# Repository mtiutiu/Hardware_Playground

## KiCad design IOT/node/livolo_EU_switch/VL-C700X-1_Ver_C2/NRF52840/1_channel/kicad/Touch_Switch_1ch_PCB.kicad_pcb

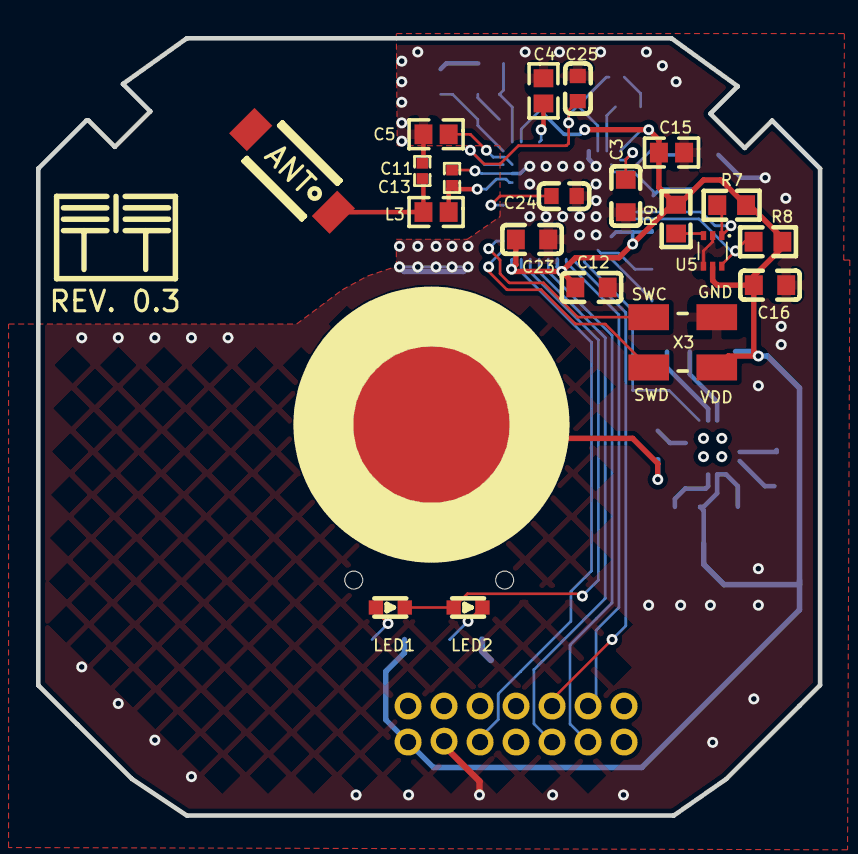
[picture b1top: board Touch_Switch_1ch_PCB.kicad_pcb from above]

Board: 2 copper layers, 43.4 x 43.2 mm, 47 parts (0 on the bottom side), 37 nets.

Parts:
ALG: my_logo; ggeac4e8891367b2b2c
C1, C15, C17: 1uF; 0603
C2, C3, C12, C16, C18, C19, C20, C23: 100nF; C0603
C4: N.C.; 0603
C5: 100pF; 0603
C6: 2.2nF; C0603
C7, C8, C9, C10: 22pF; 0603
C11, C13: 0.5pF; 0402
C14, C21, C22: 4.7uF; 0603
C24: 820pF; C0603
C25: 47nF; C0603
CN1: 2X7P; HDR-TH_14P-P2.00-V-R2-C7-S2.00_A2005HWV-2X7P
H1: PROG; CONNECTER_SMD_1.27_1X4_D180
L2: 10uH; 0603
L3: 3.3nH; 0603
L4: 15nH; 0402
LED1: RED; LED-SMD_0603-T
LED2: BLUE; LED-SMD_0603-T
R5, R6, R7, R8, R9: 4.7K; R0603
R10: 560; R0603
U1: NRF52840-QIAA-R; AQFN-73_L7.0-W7.0-P0.50-BL-EP4.8
U3: Antenna 2.4GHz; AN6520
U5: TMP112; SOT-563_L1.6-W1.2-P0.50-LS1.6-BL
U6: CY8C4014LQI-421T; QFN-16_L3.0-W3.0-P0.50-BL-EP1.7
U7: TS1; LIVOLO_TOUCH_PAD
X1: 32MHz; OSC-SMD_4P-L2.0-W1.6-BL
X2: 32.768KHz; FC-135R_L3.2-W1.5
X3: ICSP; SWD4_5032

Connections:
ANT: C11.1, L3.1, U1.H23
C4_2: C4.2, U1.A18
CH1_LED: LED1.1, LED2.2, U1.AD20
DCC: L2.1, U1.B3
DEC4_6: C1.1, C25.2, L4.2, U1.B5, U1.E24
GND: C1.2, C2.1, C3.2, C4.1, C5.2, C6.2, C7.2, C8.2, C9.1, C10.1, C11.2, C12.1, C13.2, C14.1, C15.1, C16.2, C17.1, C18.1, C19.1, C20.1, C21.1, C22.1, C23.1, C24.1, C25.1, CN1.11, H1.3, R5.2, U1.0, U1.B7, U1.F23, U5.2, U5.4, U6.7, X1.2, X1.4, X3.3
L2_2: L2.2, L4.1
L3_2: C13.1, L3.2, U3.1
LED2_1: LED2.1, R5.1
MTO: U1.AD8, U6.13
R1_RST: CN1.6, U1.AD10
R1_SET: CN1.4, U1.AD12
R2_RST: CN1.3, U1.AD16
R2_SET: CN1.5, U1.AD18
R6_1: LED1.2, R6.1
R9_1: R9.1, U5.3
R10_1: R10.1, U7.1
SCL: R7.2, U1.N1, U5.1
SDA: R8.2, U1.R1, U5.6
SWC: H1.2, U6.15
SWCLK: U1.AA24, X3.4
SWD: H1.1, U6.14
SWDIO: U1.AC24, X3.1
U1_AC5: C21.2, U1.AC5
U1_AD2: C22.2, U1.AD2
U1_C1: C3.1, U1.C1
U1_D23: C5.1, U1.D23
U1_N24: C24.2, U1.N24
U6_3: C6.1, U6.3
U6_4: C19.2, U6.4
U6_11: R10.2, U6.11
VDD: C2.2, C12.2, C14.2, C15.2, C16.1, C17.2, C18.2, C20.2, C23.2, CN1.13, H1.4, R6.2, R7.1, R8.1, R9.2, U1.A22, U1.AD14, U1.AD23, U1.B1, U1.W1, U1.Y2, U5.5, U6.5, U6.6, X3.2
VSENSE: CN1.9, U1.AD22
XC1: C7.1, U1.B24, X1.1
XC2: C8.1, U1.A23, X1.3
XL1: C9.2, U1.D2, X2.1
XL2: C10.2, U1.F2, X2.2

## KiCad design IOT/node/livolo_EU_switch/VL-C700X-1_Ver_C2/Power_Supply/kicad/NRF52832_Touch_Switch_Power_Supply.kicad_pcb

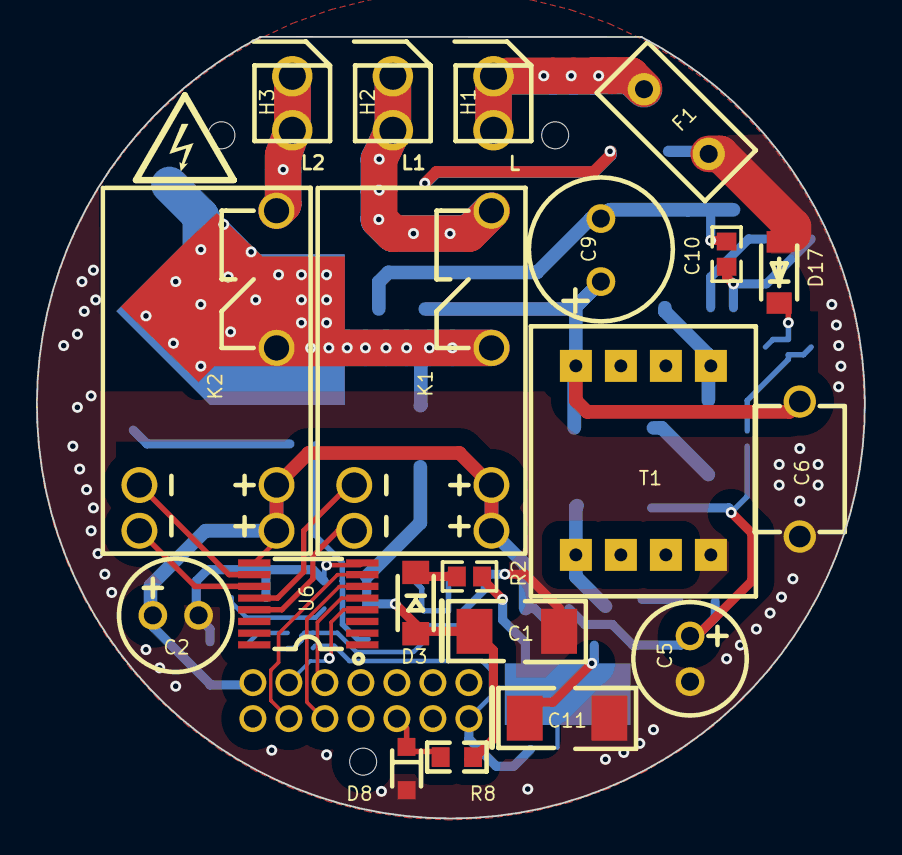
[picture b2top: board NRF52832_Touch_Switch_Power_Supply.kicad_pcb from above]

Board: 2 copper layers, 46.0 x 43.4 mm, 53 parts (1 on the bottom side), 35 nets.

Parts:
C1, C11: 22uF; CAP-SMD_L6.0-W3.2
C2, C5: 330uF; CAP-TH_BD6.3-P2.50-D1.0-FD
C3: 22uF; CP_EIA-3528-21_Kemet-B
C4: 680nF; 0805
C6: 1nF; CAP-TH_L7.0-W5.0-P7.50-D1.2
C7: 27pF; 0805
C9: 4.7uF; CAP-TH_BD8.0-P3.50-D1.0-FD
C10: 100nF; 0603
CN1: 2X7P; A2005WV-2X7P
D1: B340LB-13-F; SMB_L4.6-W3.6-LS5.3-RD
D2, D3: 1N4007W; SOD-123FL_L2.7-W1.8-LS3.8-RD
D4, D7, D12: BAV21WS; SOD-323_L1.8-W1.3-LS2.5-RD
D5, D6: MMSZ5242BS; SOD-323_L1.8-W1.3-LS2.5-RD
D8: BZT52C3V3S; SOD-323_L1.8-W1.3-LS2.5-RD
D13: MB6S; MBS
D14: SS14; SMA_L4.3-W2.6-LS5.2-FD
D15: SMBJ130A; SMB_L4.6-W3.6-LS5.3-RD
D16: US1M; SMA(DO-214AC)
D17: MMSZ5242; SOD-123_L2.8-W1.8-LS3.7-RD
F1: SMT1500A; FUSE-TH_L8.5-W4.0-P5.08-D0.6
H1: L; 360273
H2: L1; 360273
H3: L2; 360273
HV2: IEC_HighVoltage; IEC_HIGHVOLTAGE_SMALL
K1, K2: HFE60-12-1HT-L2; RELAY-TH_HFE60-12-1HST-L2
LG: my_logo; gge1185
Q1: IRLR8726PBF; TO-252-2_L6.6-W6.1-P4.57-LS9.9-BR-CW
Q2: MMBT3904; SOT-23(SOT-23-3)
R1, R2: 47; 0603
R3: 20K; 0402
R4: 10K; 0402
R5, R6: 100K; R0402
R7: 33K; 0402
R8: 1K; R0603
R16: 390; 0805
R18: 22; 0402
R19: 1K; 0402
R20: 10; 1206
T1: EE10A-1
U1: LM321; SOT-23-5_L3.0-W1.7-P0.95-LS2.8-BL
U2: MCP1703T-3302; SOT-89-3_L4.5-W2.5-P1.50-LS4.2-BR
U3: EL357; SOP-4_P2.54
U4: LNK364DN-TL; SO-8_7P-L4.9-W3.9-P1.27-LS5.9-BL-PE3
U6: TPL7407LPWR; TSSOP-16_L5.0-W4.4-P0.65-LS6.4-BL

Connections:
+3V3: C3.2, CN1.2, R4.2, U2.3
+12V: C2.1, CN1.13, D4.1, D5.1, D7.1, K1.1, K1.2, K2.1, K2.2, U6.9
AC_DC_N: D13.1, H2.1, H2.2, K1.8
C9_1: C6.2, C9.1, D13.3, D15.2, T1.1
CH1_RST: CN1.9, U6.5
CH1_SET: CN1.11, U6.4
CH2_RST: CN1.12, U6.7
CH2_SET: CN1.10, U6.6
D1_1: D1.1, D2.2, K1.5, K2.5, Q1.2
D12_2: C5.1, C7.2, D7.2, D12.2, D14.2, R18.2
D16_2: D15.1, D16.2
F1_2: F1.2, H1.1, H1.2
GND: C1.2, C2.2, C3.1, C4.1, C5.2, C6.1, C11.2, CN1.4, D1.2, D5.2, D8.2, D17.2, F1.1, Q1.3, Q2.2, R6.1, R7.1, R20.1, T1.5, U1.2, U2.1, U6.8
H3_1: H3.1, H3.2, K2.8
K1_15: K1.15, U6.12
K1_16: K1.16, U6.13
K2_15: K2.15, U6.10
K2_16: K2.16, U6.11
Q1_1: Q1.1, R1.2
Q2_1: Q2.1, R5.1
Q2_3: Q2.3, R3.1
R2_1: D3.1, R2.1
R2_2: C11.1, D4.2, D12.1, R2.2, U2.2
T1_8: D14.1, R16.1, T1.8
U1_1: C4.2, D6.2, R7.2, U1.1
U1_3: R3.2, R4.1, U1.3
U1_4: R1.1, R5.2, R6.2, U1.4
U1_5: C1.1, D2.1, D3.2, D6.1, R8.2, U1.5
U3_1: R18.1, R19.2, U3.1
U3_2: D17.1, R19.1, U3.2
U3_3: U3.3, U4.2
U3_4: C10.1, U3.4, U4.1
U4_4: D16.1, T1.4, U4.4
U4_5: C9.2, C10.2, D13.4, U4.5, U4.6, U4.7, U4.8
VSENSE: CN1.6, D8.1, R8.1

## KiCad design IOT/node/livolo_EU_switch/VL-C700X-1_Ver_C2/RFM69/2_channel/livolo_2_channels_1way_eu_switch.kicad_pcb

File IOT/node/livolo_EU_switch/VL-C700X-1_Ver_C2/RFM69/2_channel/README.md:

## Mysensors RFM69 Livolo 2 channels 1 way EU switch front module

##### 3D renderings of pcb

Top view | Bottom view
------------ | -------------
 | 

**Description:**

This is a Mysensors replica of the Livolo EU Switch(2 channels 1 way) front plate for the **VL-C702X-2_Ver_C1** Livolo hw revision.

**Key Features:**

 - **Capacitive touch sensing** using **TTP223** specialized IC
 - **AT25DF512C-SSHN-B** SPI flash module for OTA
 - **ATSHA204A** for signing
 - **MySensors** ready(Atmega328p + RFM69CW)
 - **DC-DC Buck converter** in combination with a **linear LDO voltage regulator** for efficient **noise cancelling**
  (the used LDO reduces a little bit the Buck's converter current capability - down to 150mA from 600mA but this is not important as the whole board takes about 60mA at peak)

**Work progress:**
 1. Test/verify the pcb board correctness(from both electrical and mechanical point of views) - **IN PROGRESS**
 2. Produce the initial PCB's using some external PCB manufacturer
 3. Components assembly(soldering)
 4. Create Mysensors sketch code
 5. Verify the real board with running code
 6. Verify OTA

**HW Revisions:**
 - 0.1 - initial hw design

 **Kindly notice:**

The only thing I ask if using this project is to at least mention my name and if I don't ask too much you can also support my effort using the below button. Thanks for buying me a beer :).

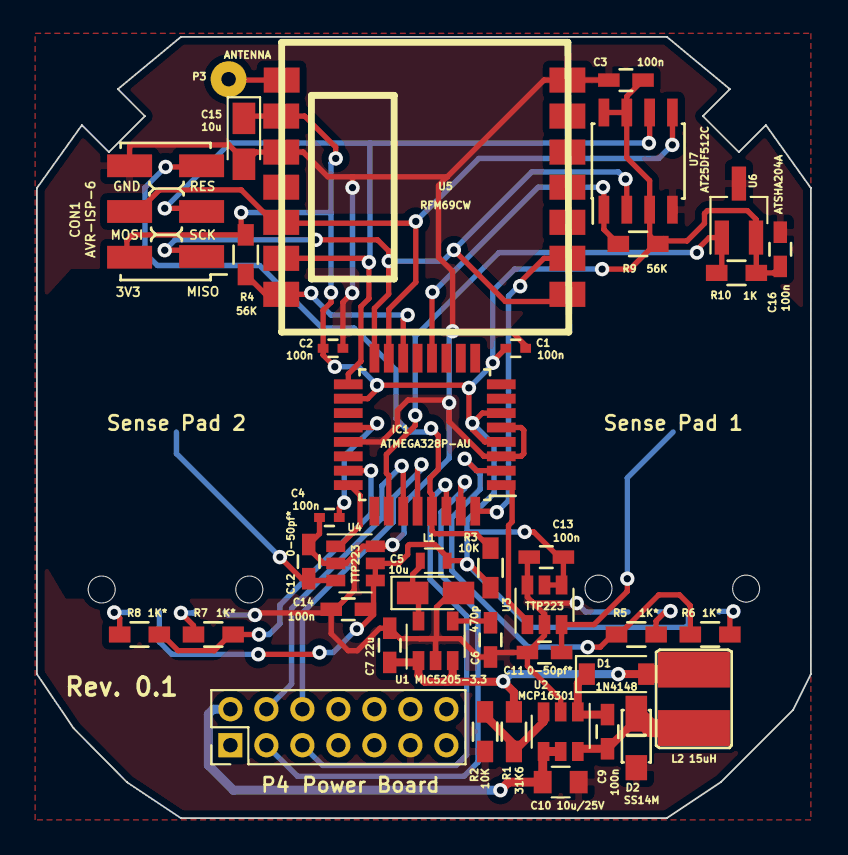
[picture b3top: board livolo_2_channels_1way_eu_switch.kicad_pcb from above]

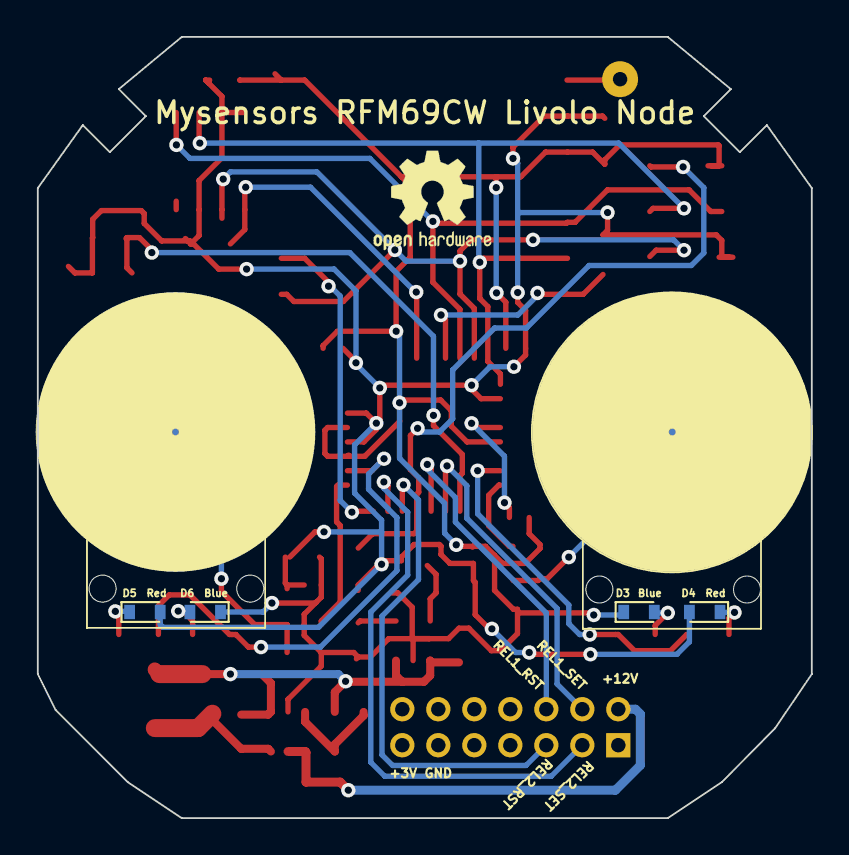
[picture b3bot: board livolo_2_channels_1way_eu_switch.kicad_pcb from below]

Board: 2 copper layers, 43.0 x 43.4 mm, 46 parts (4 on the bottom side), 33 nets.

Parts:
C1, C2, C4: 100n; C_0402
C3, C9, C13, C14, C16: 100n; C_0603_HandSoldering
C5, C15: 10u; CP_Tantalum_Case-R_EIA-2012-12_Wave
C6: 470p; C_0603_HandSoldering
C7: 22u; C_0603_HandSoldering
C10: 10u/25V; C_0805
C11, C12: 0-50pf*; C_0603_HandSoldering
CON1: AVR-ISP-6; AVR_ISP_SMT_Small_02x03
D1: 1N4148; SOD-123
D2: SS14M
D3, D6: Blue; D_0603
D4, D5: Red; D_0603
IC1: ATMEGA328P-AU; TQFP-32_7x7mm_Pitch0.8mm
L1: BLM18HE152SN1D; R_0603
L2: 15uH; VLCF4020T-150MR68
P1: Sense Pad 1; touch_pad_16mm
P2: Sense Pad 2; touch_pad_16mm
P3: ANTENNA; SolderWirePad_single_0-8mmDrill
P4: Power Board; Pin_Header_Straight_2x07_Pitch2.00mm
R1: 31K6; R_0603_HandSoldering
R2, R3: 10K; R_0603_HandSoldering
R4, R9: 56K; R_0603_HandSoldering
R5, R6, R7, R8: 1K*; R_0603_HandSoldering
R10: 1K; R_0603_HandSoldering
U1: MIC5205-3.3; SOT-23-5
U2: MCP16301; SOT-23-6
U3, U4: TTP223; SOT-23-6
U5: RFM69CW
U6: AT25DF512C; SOIC-8_3.9x4.9mm_Pitch1.27mm
U7: ATSHA204A; SOT-23_Handsoldering

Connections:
+3V3: C1.1, C2.2, C3.2, C13.1, C14.1, C15.1, C16.2, CON1.2, D4.2, D5.2, IC1.4, IC1.6, IC1.18, L1.1, R3.1, R4.2, R9.1, R10.1, U3.4, U3.5, U4.4, U4.5, U5.2, U6.3, U6.7, U6.8, U7.2
/12Vcc: C10.1, P4.2, U2.4, U2.5
/ATSHA204A: IC1.26, R10.2, U7.1
/FLASH_SS: IC1.12, R9.2, U6.1
/INT: IC1.32, U5.9
/MISO: CON1.1, IC1.16, U5.8, U6.2
/MOSI: CON1.4, IC1.15, U5.5, U6.5
/RADIO_SS: IC1.14, R4.1, U5.7
/RESET: CON1.5, IC1.29, R3.2
/Relay1_Reset: IC1.28, P4.6
/Relay1_Set: IC1.27, P4.4
/Relay2_Reset: IC1.31, P4.3
/Relay2_Set: IC1.30, P4.5
/S1_LEDs: IC1.2, R5.2, R6.2
/S2_LEDs: IC1.23, R7.2, R8.2
/SCK: CON1.3, IC1.17, U5.6, U6.6
/TS1: IC1.1, U3.1
/TS2: IC1.24, U4.1
GND: C1.2, C2.1, C3.1, C4.1, C5.2, C6.2, C7.2, C10.2, C11.2, C12.2, C13.2, C14.2, C15.2, C16.1, CON1.6, D2.2, D3.1, D6.1, IC1.3, IC1.5, IC1.21, P4.11, R2.1, U1.2, U2.2, U3.2, U3.6, U4.2, U4.6, U5.3, U5.14, U6.4, U7.3
unnamed: C4.2, IC1.20
unnamed: C5.1, L1.2, U1.5
unnamed: C6.1, U1.4
unnamed: C7.1, D1.2, L2.1, R1.2, U1.1, U1.3
unnamed: C9.1, D1.1, U2.1
unnamed: C9.2, D2.1, L2.2, U2.6
unnamed: C11.1, P1.1, U3.3
unnamed: C12.1, P2.1, U4.3
unnamed: D3.2, R7.1
unnamed: D4.1, R8.1
unnamed: D5.1, R6.1
unnamed: D6.2, R5.1
unnamed: P3.1, U5.1
unnamed: R1.1, R2.2, U2.3

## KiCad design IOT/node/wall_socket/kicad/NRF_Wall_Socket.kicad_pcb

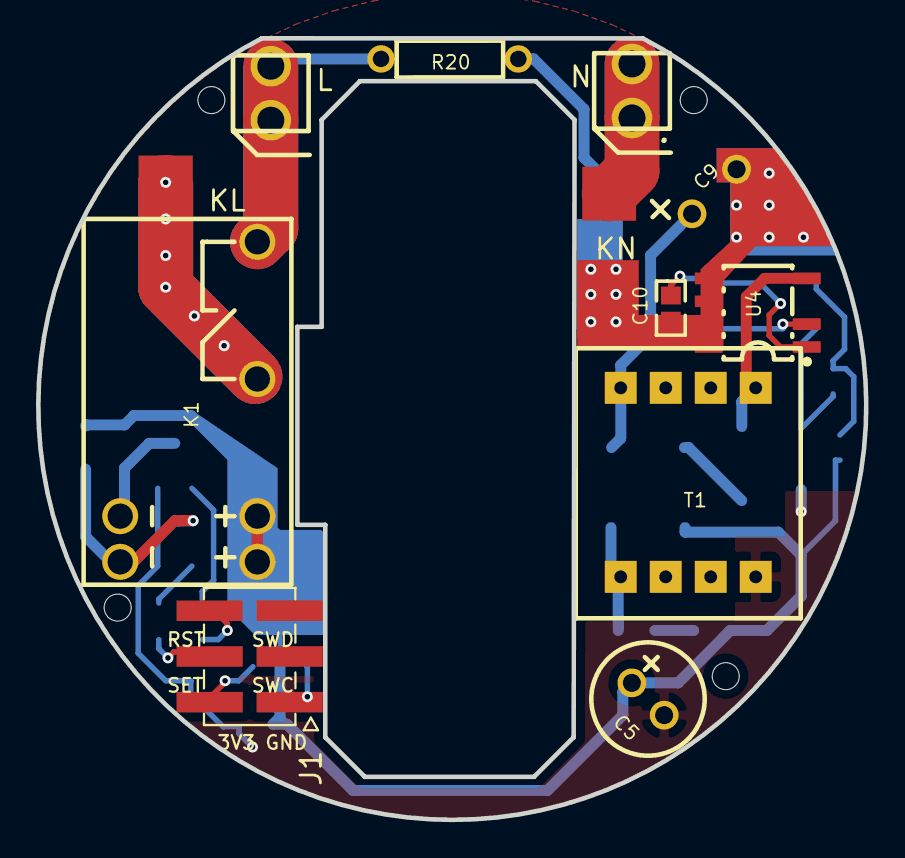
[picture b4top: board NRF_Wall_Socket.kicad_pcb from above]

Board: 2 copper layers, 46.0 x 43.4 mm, 35 parts (0 on the bottom side), 23 nets.

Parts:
BC1: _; gge3168
C1: 22uF/16V; 0805
C5: 330uF/16V; CAP-TH_BD6.3-P2.50-D1.0-FD
C7: 27pF; 0805
C9: 4.7uF/450V; CAP-TH_BD8.0-P3.50-D1.0-FD
C10: 100nF/50V; 0603
C19: 22uF/6.3V; 0805
D1, D2: 1N4148WS; SOD-323_L1.8-W1.3-LS2.5-RD
D13: MB6S; MBS
D14: SS14; SMA_L4.3-W2.6-LS5.2-FD
D15: SMBJ130A; SMB_L4.6-W3.6-LS5.3-RD
D16: US1M; SMA(DO-214AC)
D17: MMSZ5242; SOD-123_L2.8-W1.8-LS3.7-RD
HV1, HV2: IEC_HighVoltage; IEC_HIGHVOLTAGE_SMALL
J1: NRF_MODULE; 2X3_SMT
K1: HFE60-12-1HT-L2; RELAY-TH_HFE60-12-1HST-L2
KL: SW2; PAD
KN: SW1; PAD
L: L; 360273
LG: my_logo; gge4630
N: N; 360273
Q1, Q2: MMBT3904; SOT-23(SOT-23-3)
R1, R2: 4K7; 0805
R16: 390; 0805
R18, R19: 0603
R20: 10/2W; R-0.25W-JNJ-300
T1: EE10A-1
U3: EL357; SOP-4_P2.54
U4: LNK364DN-TL; SO-8_7P-L4.9-W3.9-P1.27-LS5.9-BL-PE3
U5: MCP1703T-3302; SOT-89-3_L4.5-W2.5-P1.50-LS4.2-BR

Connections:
+3V3: C19.2, J1.2, U5.3
+12V: C1.2, C5.1, C7.2, D1.1, D2.1, D14.2, K1.1, K1.2, R18.2, U5.2
C7_1: C7.1, R16.2
C10_1: C10.1, U3.4, U4.1
C10_2: C9.2, C10.2, D13.4, U4.5, U4.6, U4.7, U4.8
D13_1: D13.1, R20.2
D15_1: D15.1, D16.2
D15_2: C9.1, D13.3, D15.2, T1.1
D16_1: D16.1, T1.4, U4.4
GND: C1.1, C5.2, C19.1, D17.2, J1.1, Q1.2, Q2.2, T1.5, U5.1
K1_5: K1.5, KL.1
K1_15: D1.2, K1.15, Q2.3
K1_16: D2.2, K1.16, Q1.3
L: K1.8, L.1, L.2, R20.1
N: D13.2, KN.1, N.1, N.2
Q1_1: Q1.1, R1.1
Q2_1: Q2.1, R2.2
R16_1: D14.1, R16.1, T1.8
R18_1: R18.1, R19.1, U3.1
R19_1: D17.1, R19.2, U3.2
R_RST: J1.6, R2.1
R_SET: J1.4, R1.2
U4_2: U3.3, U4.2

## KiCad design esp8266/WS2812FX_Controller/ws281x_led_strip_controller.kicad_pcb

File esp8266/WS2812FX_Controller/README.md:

## ESP8266 WS2812FX Controller

##### 3D renderings of pcb

Top view | Bottom view
------------ | -------------
 | 

**Description:**

ESP8266 Controller for WS2812 based LED strips.

**Kindly notice:**

The only thing I ask if using this project is to at least mention my name and if I don't ask too much you can also support my effort using the below button. Thanks for buying me a beer :).

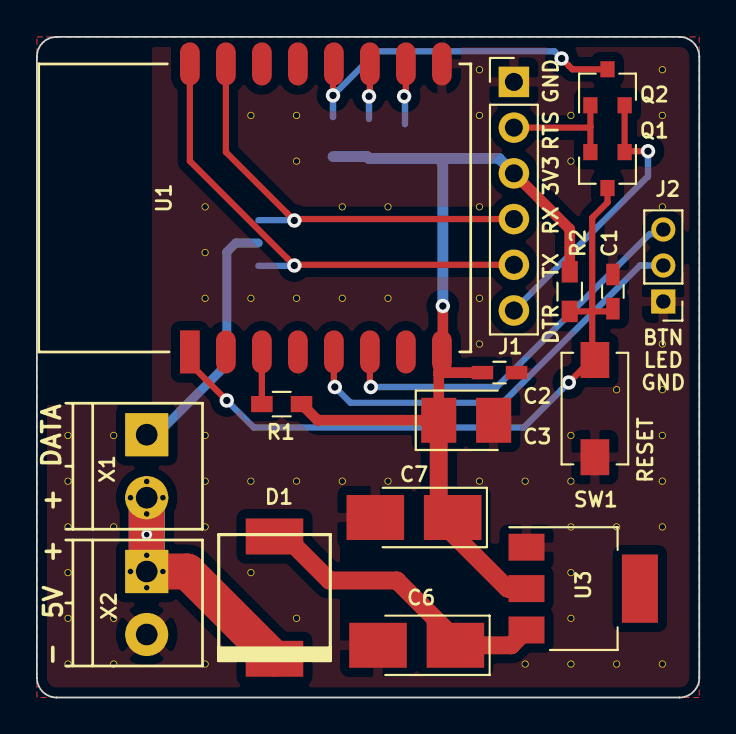
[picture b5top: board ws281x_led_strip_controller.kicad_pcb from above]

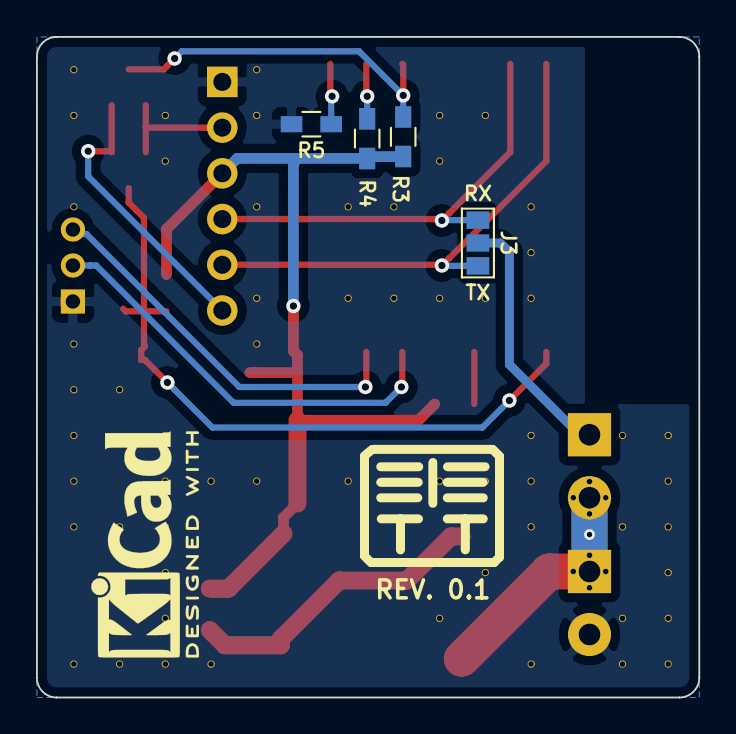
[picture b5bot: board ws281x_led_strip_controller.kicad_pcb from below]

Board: 2 copper layers, 36.8 x 36.7 mm, 81 parts (4 on the bottom side), 16 nets.

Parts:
C1, C2: 100n; C_0603_HandSoldering
C3: 22u; CP_Tantalum_Case-B_EIA-3528-21_Reflow
C6: 22u; CP_Tantalum_Case-B_EIA-3528-21_Hand
C7: 10u; CP_Tantalum_Case-B_EIA-3528-21_Hand
D1: SS34; do214ab
J1: Conn_01x06; Pin_Header_Straight_1x06_Pitch2.54mm
J2: LED_BTN; Pin_Header_Straight_1x03_Pitch2.00mm
J3: GS3
Q1, Q2: MMBT3904; SOT-23
R1, R2, R3, R4, R5: 10K; R_0603_HandSoldering
SW1: RESET; SW_SPST_EVQPE1
U1: ESP-12
U3: AMS1117-3.3; SOT-223
V1_9, V1_10, V1_11, V1_12, V1_13, V1_14, V2_9, V2_11, V2_13, V2_14, V4_4, V4_5, V4_6, V4_9, V4_10, V4_11, V4_14, V5_2, V5_6, V5_10, V5_12, V6_2, V6_3, V6_6, V6_10, V6_13, V7_4, V7_6, V7_10, V8_4, V8_6, V8_10, V10_1, V10_2, V10_4, V10_6, V10_7, V10_10, V11_10, V11_14, V12_2, V12_3, V12_9, V12_10, V12_11, V12_12, V12_13, V12_14, V13_8, V13_11, V13_14, V14_1, V14_2, V14_4, V14_7, V14_8, V14_9, V14_10, V14_11, V14_14: AUTO_VIA; VIA_MATRIX
X1: WS2812; TerminalBlock_Phoenix_PT-3.5mm_2pol
X2: 5V; TerminalBlock_Phoenix_PT-3.5mm_2pol

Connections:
+3V3: C2.1, C3.1, C7.1, J1.3, R1.2, R2.2, R3.2, R4.2, U1.8, U3.2
/DTR: J1.6, Q1.1, Q2.2
/EN: R1.1, U1.3
/GPIO0: Q2.3, R3.1, U1.12
/GPIO2: R4.1, U1.11
/GPIO15: R5.1, U1.10
/LED_BTN: J2.3, U1.6
/LED_BTN_SIGNALING: J2.2, U1.5
/RESET: C1.1, Q1.3, R2.1, SW1.1, U1.1
/RTS: J1.2, Q1.2, Q2.1
/RX: J1.4, J3.3, U1.15
/TX: J1.5, J3.1, U1.16
/WS2812_DATA: J3.2, X1.1
GND: C1.2, C2.2, C3.2, C6.2, C7.2, J1.1, J2.1, R5.2, SW1.2, U1.9, U3.1, V1_9.1, V1_10.1, V1_11.1, V1_12.1, V1_13.1, V1_14.1, V2_9.1, V2_11.1, V2_13.1, V2_14.1, V4_4.1, V4_5.1, V4_6.1, V4_9.1, V4_10.1, V4_11.1, V4_14.1, V5_2.1, V5_6.1, V5_10.1, V5_12.1, V6_2.1, V6_3.1, V6_6.1, V6_10.1, V6_13.1, V7_4.1, V7_6.1, V7_10.1, V8_4.1, V8_6.1, V8_10.1, V10_1.1, V10_2.1, V10_4.1, V10_6.1, V10_7.1, V10_10.1, V11_10.1, V11_14.1, V12_2.1, V12_3.1, V12_9.1, V12_10.1, V12_11.1, V12_12.1, V12_13.1, V12_14.1, V13_8.1, V13_11.1, V13_14.1, V14_1.1, V14_2.1, V14_4.1, V14_7.1, V14_8.1, V14_9.1, V14_10.1, V14_11.1, V14_14.1, X2.2
unnamed: C6.1, D1.1, U3.3
unnamed: D1.2, X1.2, X2.1

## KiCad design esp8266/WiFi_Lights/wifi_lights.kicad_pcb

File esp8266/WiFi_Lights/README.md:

## WiFi Lights Actuator ESPEasy module

##### 3D renderings of pcb

Top view | Bottom view
------------ | -------------
 | 

**Description:**

This is a WiFi Lights Actuator based on ESP8266 for ESPEasy project

**Key Features:**

 - **ESP8266** WiFi SOC
 - **HLK-PM01** compact AC/DC switching power supply
 - **H3V4F** 433Mhz/3.3V ASK radio receiver

**Work progress:**

 1. Test/verify the pcb board correctness(from both electrical and mechanical point of views) - **DONE**
 2. Produce the initial PCB's using some external PCB manufacturer - **IN PROGRESS**
 3. Components assembly(soldering)
 4. Create 3D printed plastic enclosure
 5. Flash ESPEasy
 6. Verify the real board with running code

**Note: Work in progress(schematic/pcb will change).**

**HW Revisions:**
 - 0.1 - initial hw design

**Kindly notice:**

The only thing I ask if using this project is to at least mention my name and if I don't ask too much you can also support my effort using the below button. Thanks for buying me a beer :).

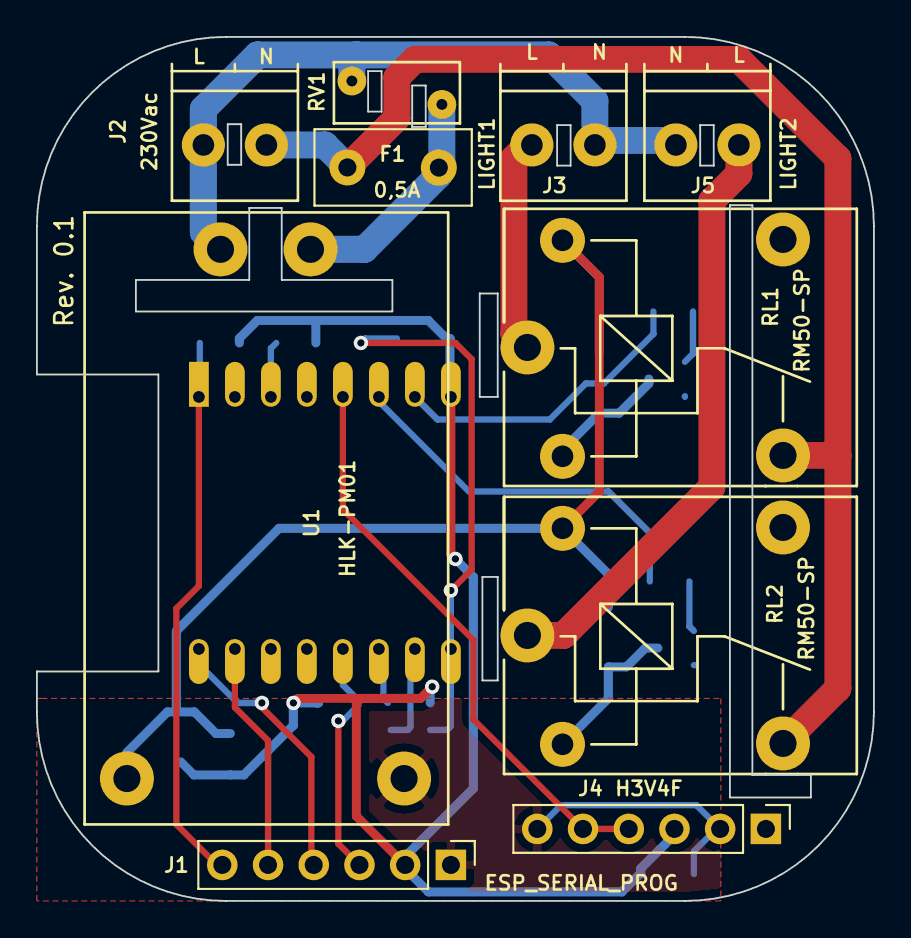
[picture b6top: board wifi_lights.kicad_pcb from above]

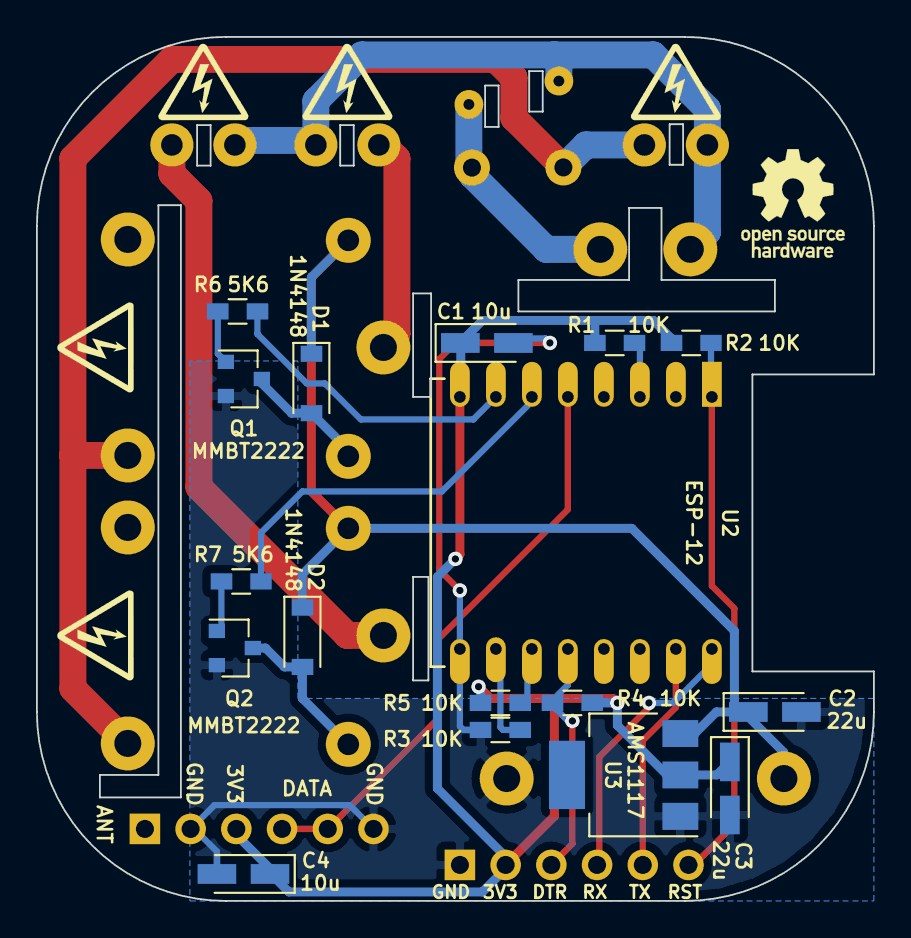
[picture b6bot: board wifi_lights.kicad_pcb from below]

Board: 2 copper layers, 46.5 x 48.0 mm, 27 parts (17 on the bottom side), 22 nets.

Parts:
C1, C4: 10u; CP_Tantalum_Case-A_EIA-3216-18_Wave
C2, C3: 22u; CP_Tantalum_Case-A_EIA-3216-18_Wave
D1, D2: 1N4148; D_SOD-123
F1: 0,5A; Fuse_TE5_Littlefuse-395Series
J1: ESP_SERIAL_PROG; Pin_Header_Straight_1x06_Pitch2.54mm
J2: 230Vac; TerminalBlock_Pheonix_PT-3.5mm_2pol
J3: LIGHT1; TerminalBlock_Pheonix_PT-3.5mm_2pol
J4: H3V4F; Pin_Header_Straight_1x06_Pitch2.54mm
J5: LIGHT2; TerminalBlock_Pheonix_PT-3.5mm_2pol
Q1, Q2: MMBT2222; SOT-23
R1, R2, R3, R4, R5: 10K; R_0603_HandSoldering
R6, R7: 5K6; R_0603_HandSoldering
RL1, RL2: RM50-SP; RM50_P
RV1: Varistor; RV_Disc_D7_W3.4_P5
U1: ESP-12
U2: HLK-PM01
U3: AMS1117; SOT-223

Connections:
+3V3: C1.1, C3.1, C4.1, J1.2, J4.3, R1.2, R2.2, R4.2, R5.2, U1.8, U3.2
+5V: C2.1, D1.1, D2.1, RL1.A1, RL2.A1, U2.3, U3.3
/433_RX_DATA: J4.4, J4.5, U1.5
/DTR: J1.3, R4.1, U1.12
/L: F1.1, J2.1, RL1.14, RL2.14
/N: J2.2, J3.1, J5.2, RV1.2, U2.2
/RELAY_CH1: R6.2, U1.7
/RELAY_CH2: R7.2, U1.6
/REL_SW1: J3.2, RL1.11
/REL_SW2: J5.1, RL2.11
/RESET: J1.6, R2.1, U1.1
/RX: J1.4, U1.16
/TX: J1.5, U1.15
GND: C1.2, C2.2, C3.2, C4.2, J1.1, J4.2, J4.6, Q1.2, Q2.2, R3.1, U1.9, U2.4, U3.1
unnamed: D1.2, Q1.3, RL1.A2
unnamed: D2.2, Q2.3, RL2.A2
unnamed: F1.2, RV1.1, U2.1
unnamed: Q1.1, R6.1
unnamed: Q2.1, R7.1
unnamed: R1.1, U1.3
unnamed: R3.2, U1.10
unnamed: R5.1, U1.11
